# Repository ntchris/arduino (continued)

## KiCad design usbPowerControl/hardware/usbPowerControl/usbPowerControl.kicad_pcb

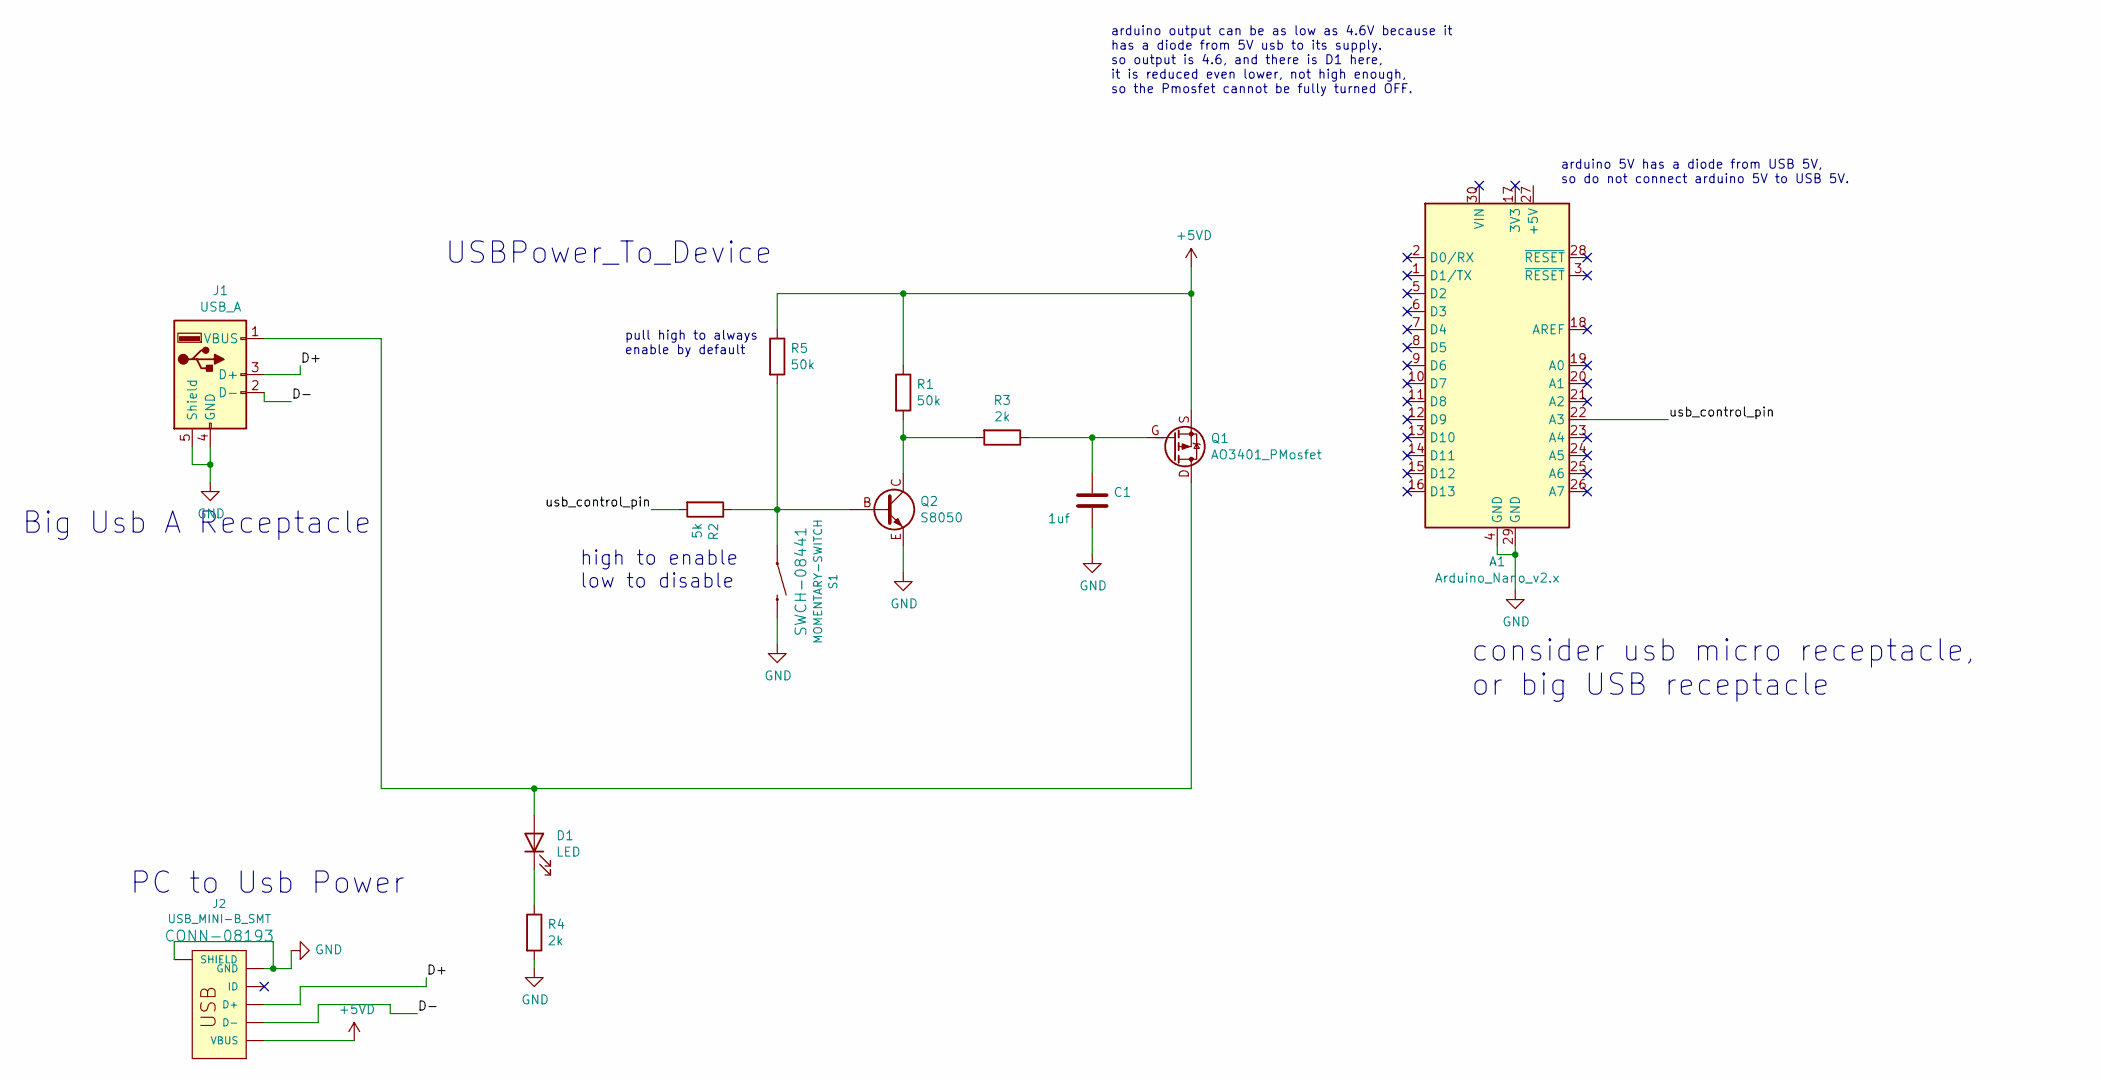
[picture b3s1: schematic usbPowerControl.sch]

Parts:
A1: Arduino_Nano_v2.x; Arduino_Nano
C1: 1uf; R_C_0805_2012Metric_Pad1.20x1.50mm_HandSolder
D1: LED; LED_D3.0mm
J1: USB_A; SAMTEC_USB-A-S-X-X-SM2
J2: USB_MINI-B_SMT; USB_Mini-B_Wuerth_65100516121_Horizontal
Q1: AO3401_PMosfet; SOT-23_PMOSFET
Q2: S8050; SOT-23_PNP_NPN
R1: 50k; R_C_0805_2012Metric_Pad1.20x1.50mm_HandSolder
R2: 5k; R_C_0805_2012Metric_Pad1.20x1.50mm_HandSolder
R3, R4: 2k; R_C_0805_2012Metric_Pad1.20x1.50mm_HandSolder
R5: 50k; R_1206_3216Metric_Pad1.30x1.75mm_HandSolder
S1: MOMENTARY-SWITCH; SW_Push_1P1T_NO_6x6mm_H9.5mm

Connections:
+5VD: J2.VBUS, Q1.S, R1.1, R5.1
/D+: J1.3 (D+), J2.D+
/D-: J1.2 (D-), J2.D-
/usb_control_pin: A1.22 (A3), R2.2
GND: A1.4 (GND), A1.29 (GND), C1.2, J1.4 (GND), J1.5 (Shield), J1.6, J2.GND, J2.S1 (SHIELD), J2.S2 (SHIELD), J2.S3 (SHIELD), J2.S4 (SHIELD), Q2.E, R4.2, S1.2
unnamed: C1.1, Q1.G, R3.1
unnamed: D1.A, J1.1 (VBUS), Q1.D
unnamed: D1.K, R4.1
unnamed: Q2.B, R2.1, R5.2, S1.1
unnamed: Q2.C, R1.2, R3.2

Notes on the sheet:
PC to Usb Power
USBPower_To_Device
Big Usb A Receptacle
consider usb micro receptacle, or big USB receptacle
arduino output can be as low as 4.6V because it has a diode from 5V usb to its supply. so output is 4.6, and there is D1 here, it is reduced even lower, not high enough, so the Pmosfet cannot be fully turned OFF.
high to enable low to disable
pull high to always enable by default
arduino 5V has a diode from USB 5V, so do not connect arduino 5V to USB 5V.

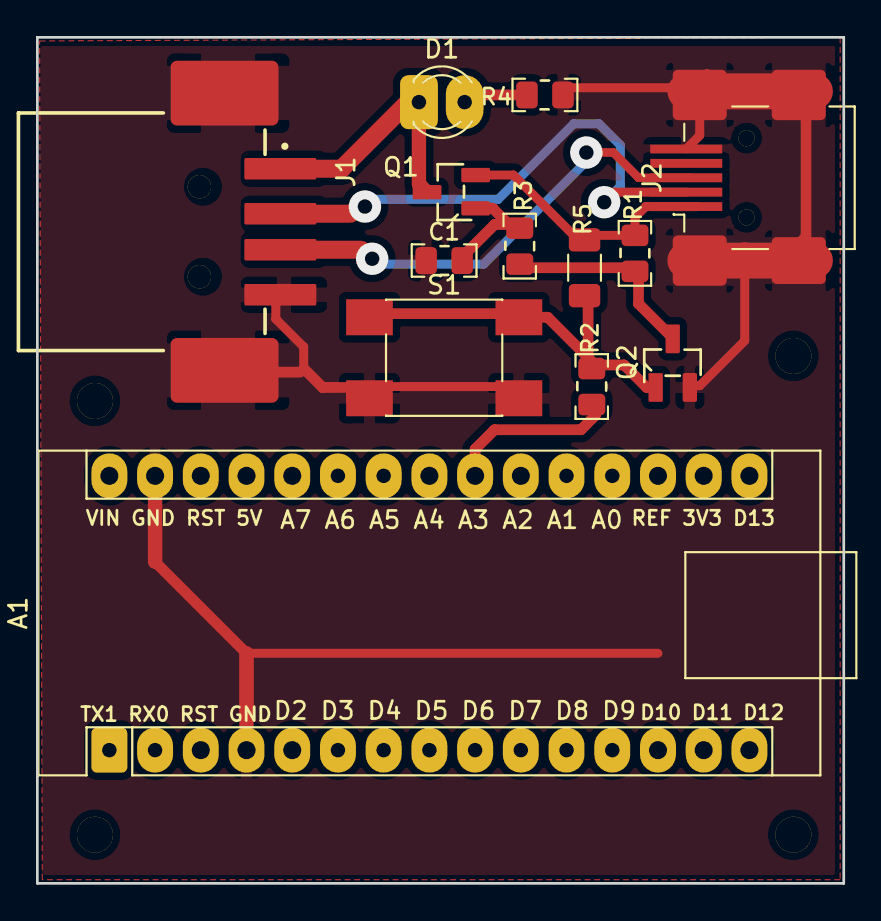
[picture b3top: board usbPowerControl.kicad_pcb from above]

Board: 2 copper layers, 44.8 x 47.0 mm, 13 parts (0 on the bottom side), 10 nets.

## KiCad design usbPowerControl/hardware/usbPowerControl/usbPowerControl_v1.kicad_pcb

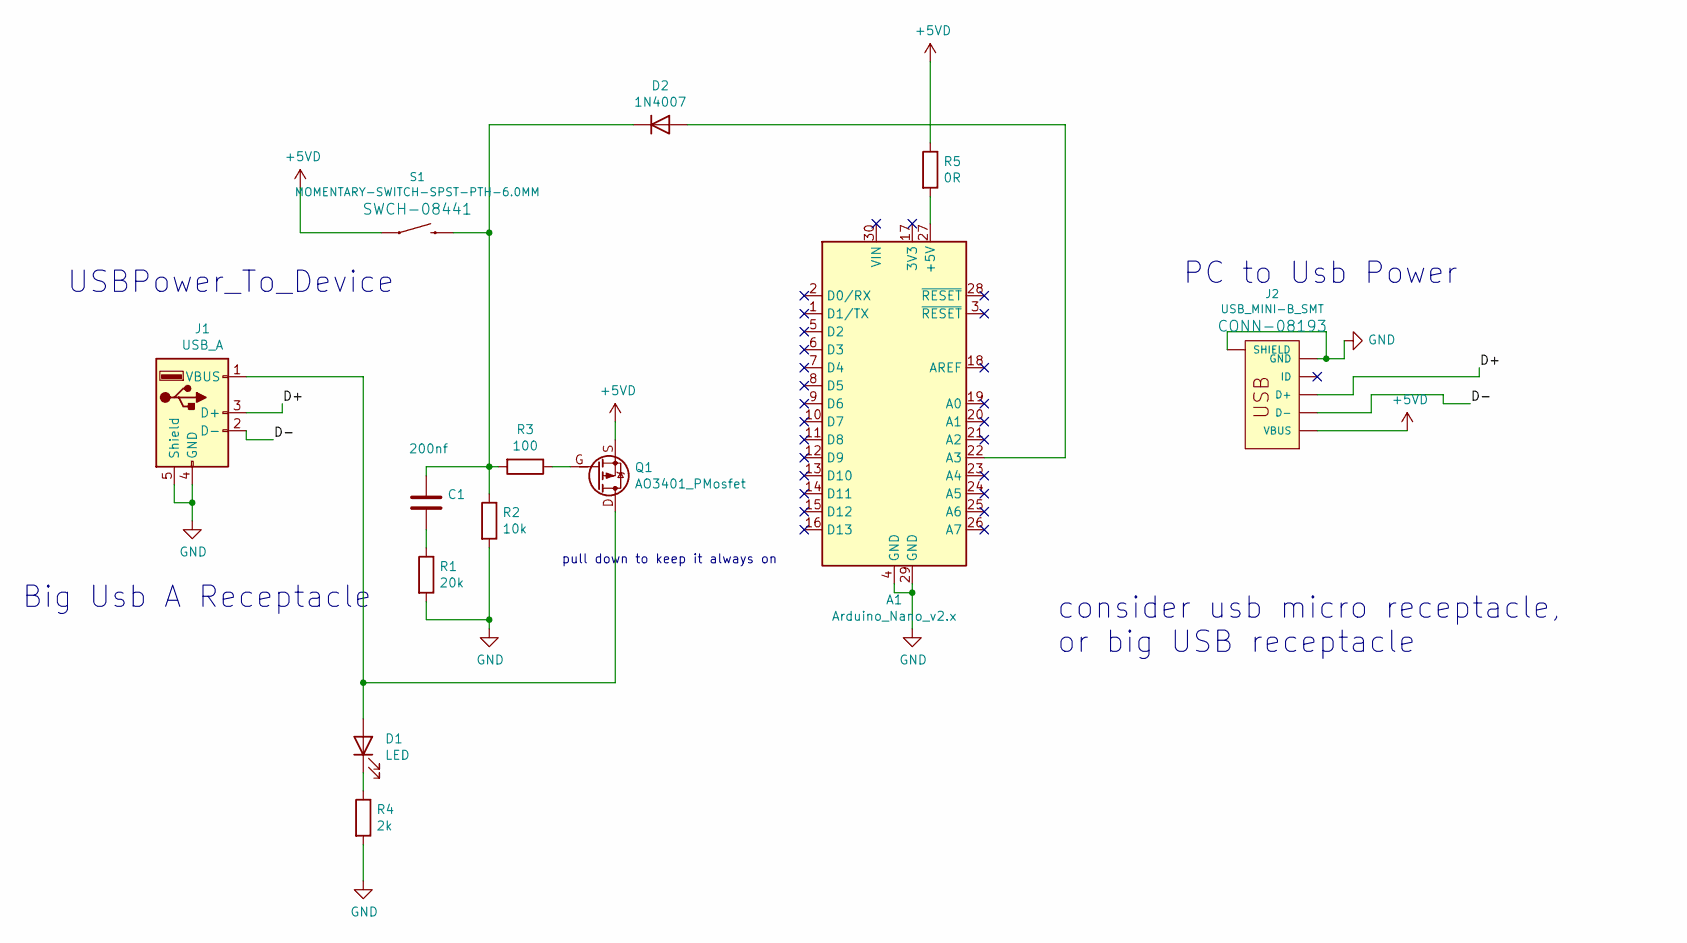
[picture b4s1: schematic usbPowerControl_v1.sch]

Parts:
A1: Arduino_Nano_v2.x; Arduino_Nano
C1: 200nf; R_C_0805_2012Metric_Pad1.20x1.50mm_HandSolder
D1: LED; LED_D3.0mm
D2: 1N4007; D_SOD-323_HandSoldering
J1: USB_A; SAMTEC_USB-A-S-X-X-SM2
J2: USB_MINI-B_SMT; USB_Mini-B_Wuerth_65100516121_Horizontal
Q1: AO3401_PMosfet; SOT-23_PMOSFET
R1: 20k; R_C_0805_2012Metric_Pad1.20x1.50mm_HandSolder
R2: 10k; R_C_0805_2012Metric_Pad1.20x1.50mm_HandSolder
R3: 100; R_C_0805_2012Metric_Pad1.20x1.50mm_HandSolder
R4: 2k; R_C_0805_2012Metric_Pad1.20x1.50mm_HandSolder
R5: 0R; R_C_0805_2012Metric_Pad1.20x1.50mm_HandSolder
S1: MOMENTARY-SWITCH-SPST-PTH-6.0MM; SW_Push_1P1T_NO_6x6mm_H9.5mm

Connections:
+5VD: J2.VBUS, Q1.S, R5.1, S1.1
/D+: J1.3 (D+), J2.D+
/D-: J1.2 (D-), J2.D-
GND: A1.4 (GND), A1.29 (GND), J1.4 (GND), J1.5 (Shield), J1.6, J2.GND, J2.S1 (SHIELD), J2.S2 (SHIELD), J2.S3 (SHIELD), J2.S4 (SHIELD), R1.2, R2.2, R4.2
unnamed: A1.22 (A3), D2.2 (A)
unnamed: A1.27 (+5V), R5.2
unnamed: C1.1, D2.1 (K), R2.1, R3.2, S1.2
unnamed: C1.2, R1.1
unnamed: D1.A, J1.1 (VBUS), Q1.D
unnamed: D1.K, R4.1
unnamed: Q1.G, R3.1

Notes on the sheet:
PC to Usb Power
USBPower_To_Device
Big Usb A Receptacle
consider usb micro receptacle, or big USB receptacle
pull down to keep it always on

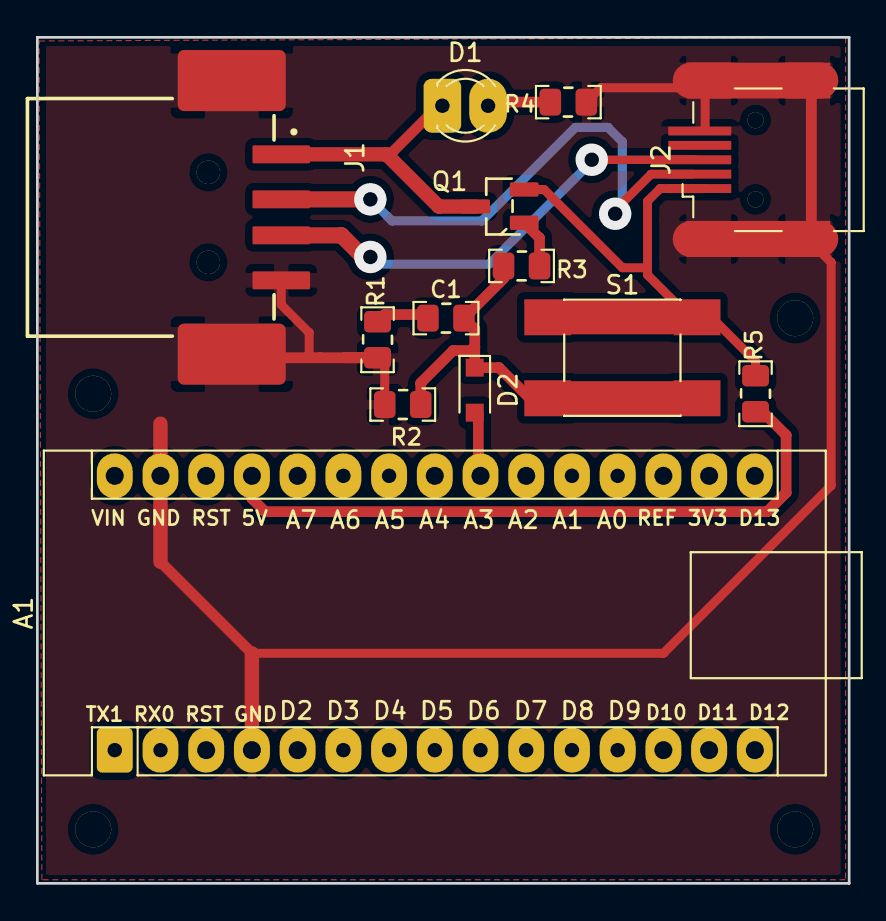
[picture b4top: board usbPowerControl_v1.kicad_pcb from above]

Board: 2 copper layers, 45.1 x 47.0 mm, 13 parts (0 on the bottom side), 11 nets.

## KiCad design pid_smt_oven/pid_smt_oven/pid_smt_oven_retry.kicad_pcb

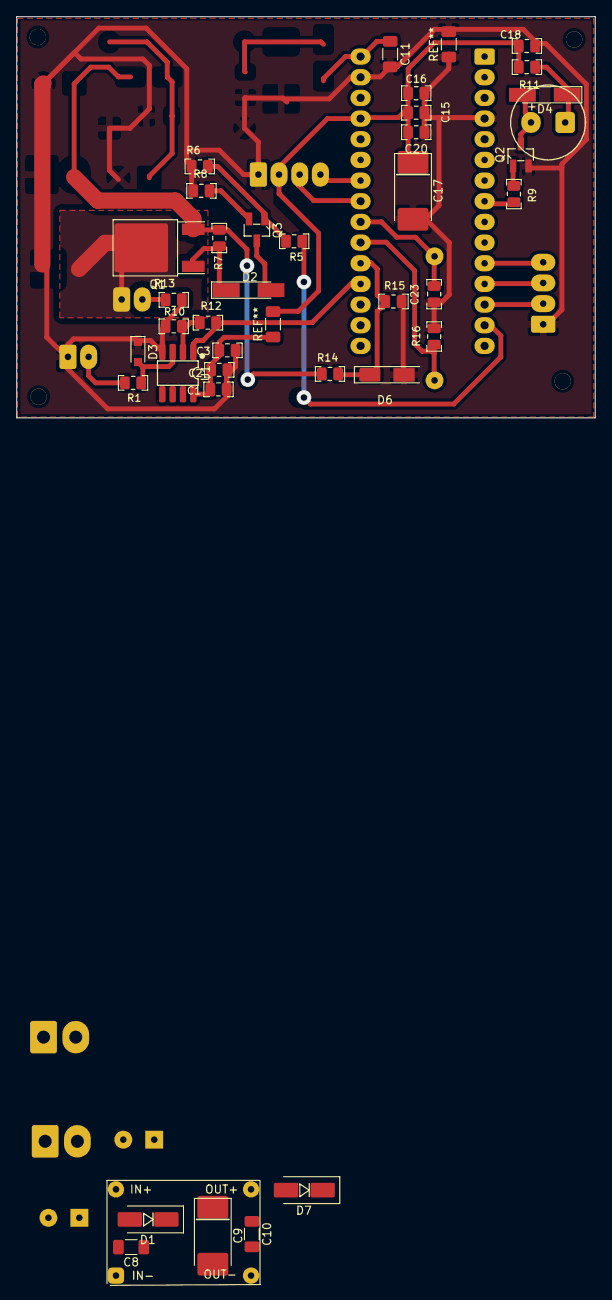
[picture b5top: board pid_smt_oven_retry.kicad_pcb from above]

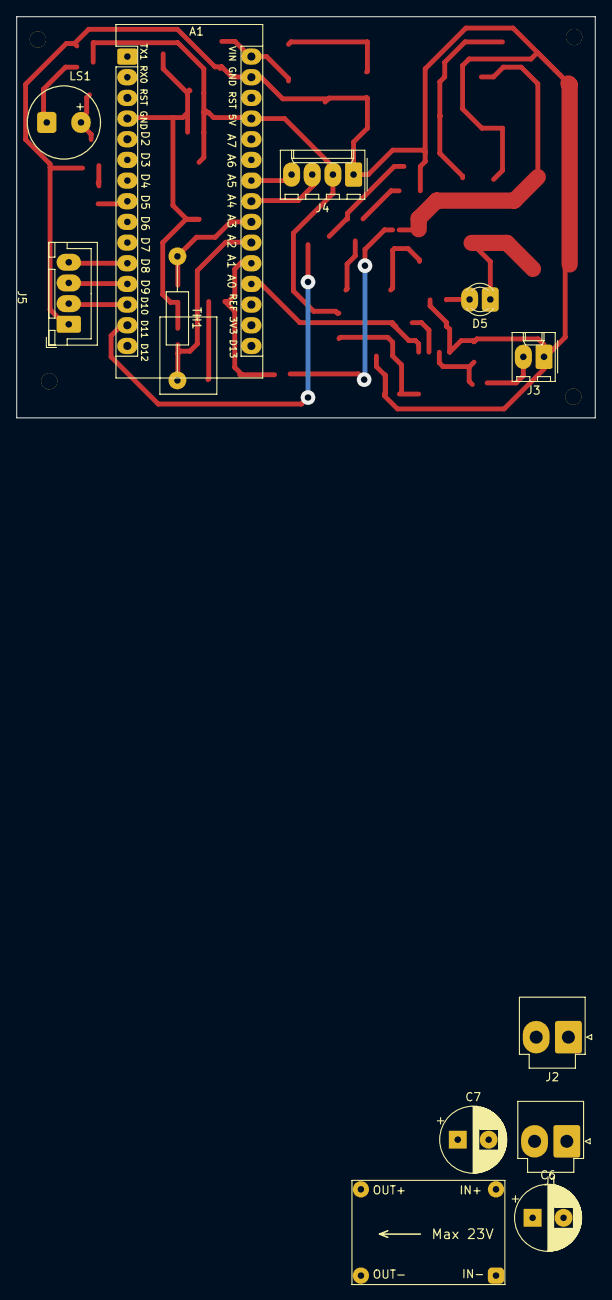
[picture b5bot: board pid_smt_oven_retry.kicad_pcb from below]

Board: 2 copper layers, 71.1 x 49.3 mm, 52 parts (12 on the bottom side), 29 nets.

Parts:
A1: Arduino_Nano_v2.x; Arduino_Nano
C1, C15, C18: 22uf; R_C_0805_2012Metric_Pad1.20x1.50mm_HandSolder
C2, C20, C23: 100nf; R_C_0805_2012Metric_Pad1.20x1.50mm_HandSolder
C3: 10nf; R_C_0805_2012Metric_Pad1.20x1.50mm_HandSolder
C6, C7: 470uf; CP_Radial_D8.0mm_P3.80mm
C8, C10: 22uf; C_1206_3216Metric_Pad1.33x1.80mm_HandSolder
C9, C17: 220uf; CP_EIA-7343-20_Kemet-V_Pad2.25x2.55mm_HandSolder
C11: 47uf; C_1206_3216Metric_Pad1.33x1.80mm_HandSolder
C16: 47uf; R_C_0805_2012Metric_Pad1.20x1.50mm_HandSolder
D1, D7: 1N4007; D_SMA_Handsoldering
D2: 5V; D_MiniMELF_Handsoldering
D3: 1N5819 S4; D_SOD-323_HandSoldering
D4: 1N4148; D_MiniMELF_Handsoldering
D5: LED; LED_D3.0mm
D6: 4v; D_MiniMELF_Handsoldering_Zener
H1, H2, H3, H4: MountingHole; MountingHole_2.0mm
J1: VH3.96_1X02 20V Power; JST_VH_B2P-VH-B_1x02_P3.96mm_Vertical
J2: Heater VH3.96_1X02; JST_VH_B2P-VH-B_1x02_P3.96mm_Vertical
J3: Thermo JST_2.54_1X02; Molex_KK-254_AE-6410-02A_1x02_P2.54mm_Vertical
J4: JST_2.54_1X04_LCD; Molex_KK-254_AE-6410-04A_1x04_P2.54mm_Vertical
J5: XH2.54_1X04_RotaryEnc; JST_XH_1x04_P2.54mm_Vertical
LS1: Speaker; Buzzer_9x4.2
Q1: AOD403_pmosfet; TO-252-2
Q2, Q3: S8050; SOT-23_PNP_NPN
R1: 10k; R_C_0805_2012Metric_Pad1.20x1.50mm_HandSolder
R5, R9, R13: 4k; R_C_0805_2012Metric_Pad1.20x1.50mm_HandSolder
R6: 18k; R_C_0805_2012Metric_Pad1.20x1.50mm_HandSolder
R7, R16: 2k; R_C_0805_2012Metric_Pad1.20x1.50mm_HandSolder
R8: 180; R_C_0805_2012Metric_Pad1.20x1.50mm_HandSolder
R10: 1k; R_C_0805_2012Metric_Pad1.20x1.50mm_HandSolder
R11: 280; R_C_0805_2012Metric_Pad1.20x1.50mm_HandSolder
R12: 240k; R_C_0805_2012Metric_Pad1.20x1.50mm_HandSolder
R14: 75k; R_C_0805_2012Metric_Pad1.20x1.50mm_HandSolder
R15: 20k; R_C_0805_2012Metric_Pad1.20x1.50mm_HandSolder
TH1: Thermistor_NTC 10k; R_Axial_DIN0207_L6.3mm_D2.5mm_P15.24mm_Horizontal
U1: MCP6002; SO-8_3.9x4.9mm_P1.27mm
a1: mini360_dcdc_stepdown; mini360_dcdc_buck_module

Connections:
20V: C6.1, D1.2, J1.2, Q1.S, R7.2, R14.1
/20VDetect: A1.20, D6.1, R14.2, R15.1
/V6.0: A1.30, C11.1, D7.1
/buzzerPwm: A1.8, R9.2
/enable_env_temp_check: A1.22, C23.1, TH1.1
/enable_heater: A1.14, R5.2
/env_temp_adc: A1.21, R16.1, TH1.2
/heaterPower: D5.A, J2.2, Q1.D
/opamp_to_adc: A1.19, R12.1, U1.1
/rot_button: A1.11, J5.4
/rot_left: A1.12, J5.3
/rot_right: A1.13, J5.2
/scl: A1.24, J4.4
/sda: A1.23, J4.3
/thermal_couple: J3.2, R1.2
GND: A1.4, A1.29, C1.2, C2.2, C3.2, C6.2, C7.2, C8.2, C9.2, C10.2, C11.2, C15.2, C16.2, C17.2, C18.2, C20.2, C23.2, D3.1, D6.2, J1.1, J2.1, J3.1, J4.1, J5.1, Q2.E, R6.2, R8.1, R10.2, R13.1, R15.2, R16.2, U1.4, a1.1, a1.4
unnamed: C7.1, C8.1, D1.1, a1.2
unnamed: C9.1, C10.1, D7.2, a1.3
unnamed: D2.1, Q1.G, R7.1
unnamed: D2.2, Q3.C
unnamed: D3.2, R1.1, U1.3
unnamed: D4.1, LS1.1, R11.2
unnamed: D4.2, LS1.2, Q2.C
unnamed: D5.K, R13.2
unnamed: Q2.B, R9.1
unnamed: Q3.B, R5.1, R6.1
unnamed: Q3.E, R8.2
unnamed: R10.1, R12.2, U1.2
V5.0: A1.27, C1.1, C2.1, C3.1, C15.1, C16.1, C17.1, C18.1, C20.1, J4.2, R11.1, U1.8

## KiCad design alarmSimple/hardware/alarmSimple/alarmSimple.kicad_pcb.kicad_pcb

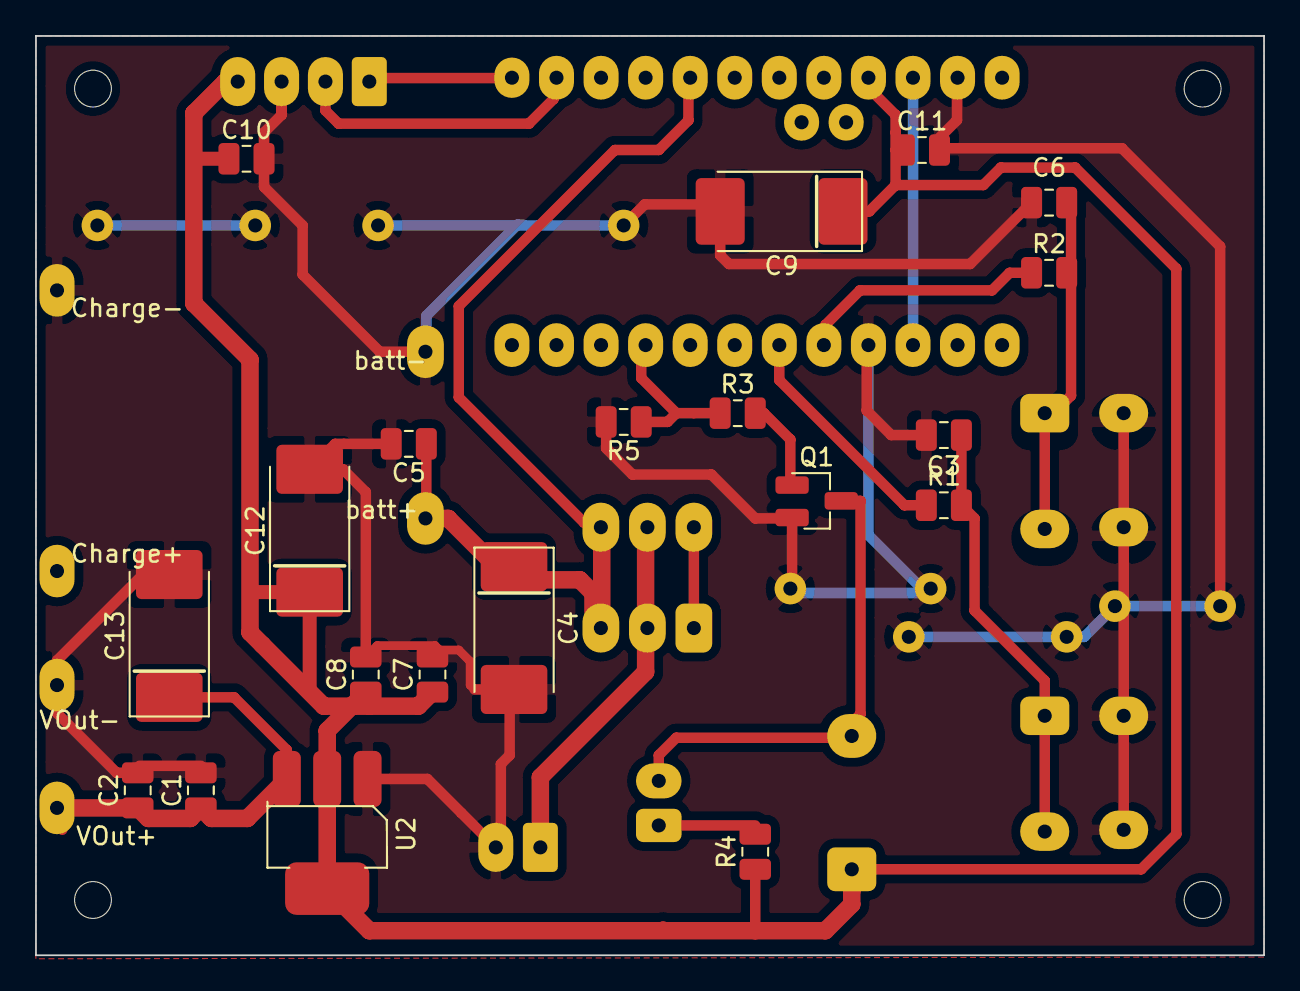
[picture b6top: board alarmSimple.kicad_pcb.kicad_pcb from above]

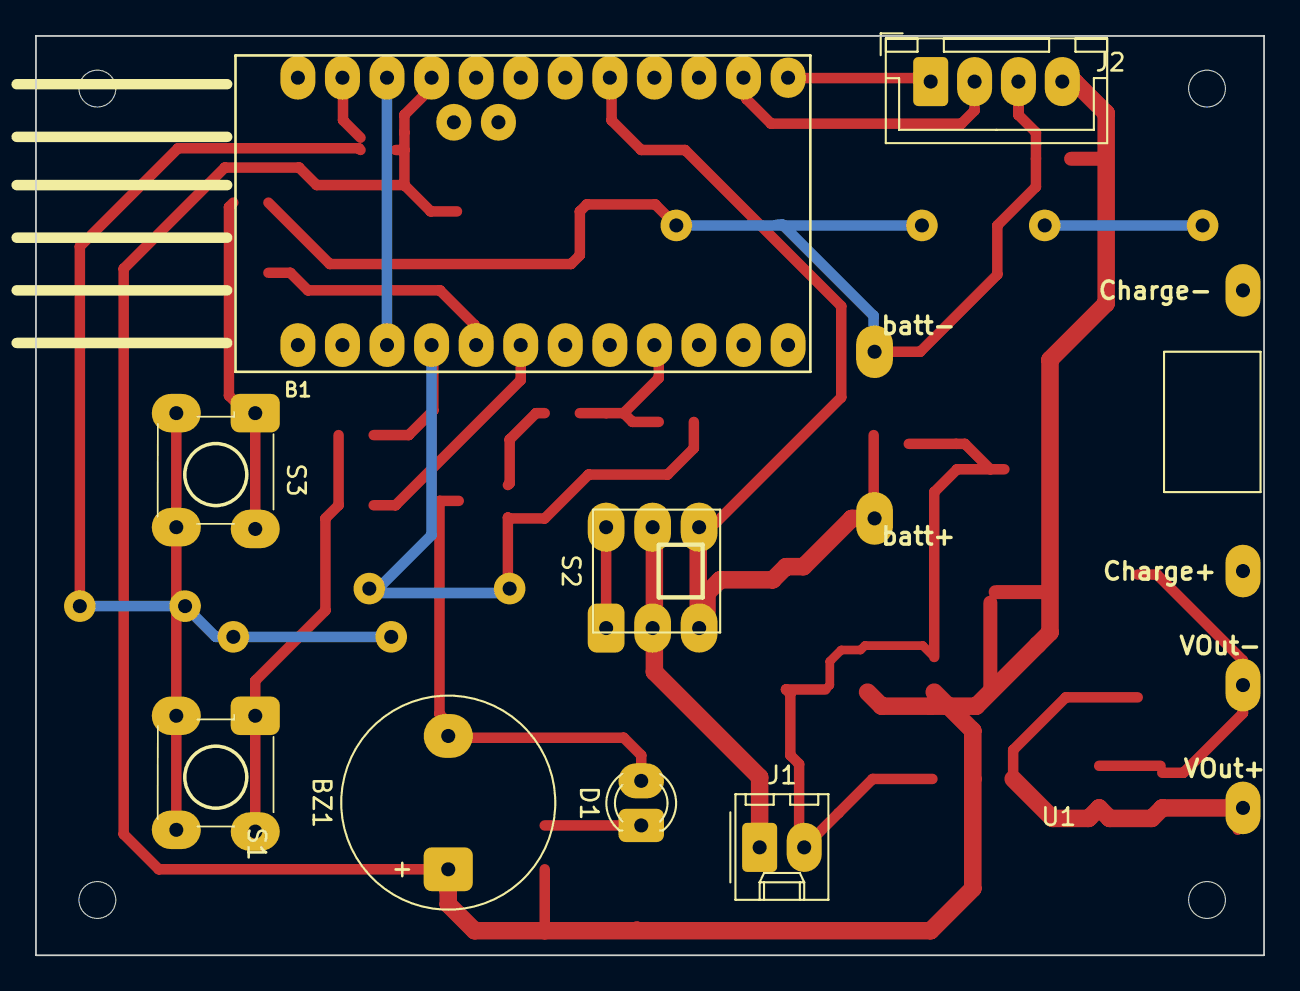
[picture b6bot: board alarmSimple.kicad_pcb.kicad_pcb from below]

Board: 2 copper layers, 70.0 x 52.4 mm, 30 parts (9 on the bottom side), 15 nets.

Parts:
 : MountingHole_2.1mm
B1: ARDUINO_PRO_MINI; arduino_pro_mini
BZ1: Buzzer; Buzzer_12x9.5RM7.6
C1: 20UF-0805-10V-10%; R_C_0805_2012Metric_Pad_HandSolder
C2, C5, C7, C8, C10, C11: 10UF-0805-10V-10%; R_C_0805_2012Metric_Pad_HandSolder
C3, C6: 100nf; R_C_0805_2012Metric_Pad_HandSolder
C4, C9, C12, C13: 220uf_227A; CP_EIA-7343-20_Kemet-V_Pad2.25x2.55mm_HandSolder
D1: LED3MM; LED_D3.0mm
J1: Batt; Molex_KK-254_AE-6410-02A_1x02_P2.54mm_Vertical
J2: Conn_01x04_Male; JST_XH_B4B-XH-A_1x04_P2.50mm_Vertical
Q1: AO3402_N_Mosfet; SOT-23_PMOSFET
R1, R2: 6.4k; R_C_0805_2012Metric_Pad_HandSolder
R3: 100R; R_C_0805_2012Metric_Pad_HandSolder
R4: 600R; R_C_0805_2012Metric_Pad_HandSolder
R5: 10kR; R_C_0805_2012Metric_Pad_HandSolder
S1, S3: MOMENTARY-SWITCH-SPST-PTH-6.0MM; Switch_Tactile_THT_6x6mm
S2: SWITCH-SPDT-PTH-11.6X4.0MM-KIT; SW_PUSH_LOCK__8.5mm_H8.5mm
U1: chargeBoostBoard; TC4056ChargeBoostBoard
U2: AMS1117-5.0; SOT-223-3_TabPin2

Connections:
+5V: B1.VCC, BZ1.1, C7.1, C8.1, C9.1, C10.1, C11.1, C12.1, J2.4, R4.1, U2.2
GND: B1.GND, C1.2, C2.2, C3.2, C4.2, C5.2, C6.2, C7.2, C8.2, C9.2, C10.2, C11.2, C12.2, C13.2, J1.2, J2.3, Q1.S, R5.2, S1.2, S3.2, U1.1, U1.3, U1.6, U2.1
unnamed: B1.10, J2.1
unnamed: B1.11, J2.2
unnamed: BZ1.2, D1.K, Q1.D
unnamed: C1.1, C2.1, C13.1, U1.4, U2.3
unnamed: C3.1, R1.2, S1.1
unnamed: C6.1, R2.2, S3.1
unnamed: D1.A, R4.2
unnamed: J1.1, S2.signal
unnamed: Q1.G, R3.2
VBattCheck: B1.A0, C4.1, C5.1, S2.close, U1.5
button_minus: B1.2, R2.1
button_plus: B1.3, R1.1
buzz_en: B1.6, R3.1, R5.1

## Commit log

2016-01-09 :octocat: Added .gitattributes
2016-01-09 Arduino first submission
    Arduino first submission
2016-05-01 First MCU AT89S51 digit tube display and counter
    First MCU AT89S51 digit tube display and counter
2016-05-02 using interrupt
2016-05-03 final , counter ready
2016-06-03 submit hex file
2016-11-29 start my TM1637 arduino project
    start my TM1637 arduino project
2016-11-29 first commit for TM1637 project
2016-11-29 delete , not in the right folder
    delete , not in the right folder
2016-12-02 Add files via upload
    it can show positive integer
2016-12-03 refactor
    add a myI2CDriver class so hopefully other ICs could reuse it.
2016-12-03 all ready
    support dot and string.
2016-12-04 supports overflow
    supports overflow
2016-12-04 error handling and set brightness
    error handling and set brightness
2016-12-04 final
2016-12-26 Create LICENSE
2018-01-22 submit a lot changes in a year
2018-01-22 minor change
2018-01-24 submit timer delay shut down project
2018-01-25 relay delay prototype is finished.
2018-01-26 reset key value if fail to get ack
2018-02-12 submit rotary encoder driver code
2018-02-13 make the rotary encoder a class
2018-02-15 change class name to super, DIO mode using input
2018-02-15 timerDigit tube project change lib name using super
    also remove hex files
2018-02-18 soldar station temp controller
    soldar station temp controller
2018-02-19 1st working draft of solder controller
2018-02-20 display less
2018-03-03 pcb design done
2018-03-03 update lib i2c dio using input pullup
2018-03-04 redraw pcb
2018-03-11 diy solder in progress also update tm1637 to display more letters
2018-03-11 rotary encoder improvement
2018-03-13 update tm1637 lib to support more chars
2018-03-13 submit draft program and schematic
2018-03-13 adding new change for disable enable heaters
2018-03-13 fix can't compile in linux problem
2018-03-13 now can compile in linux
2018-03-14 working in progress
2018-03-15 WIP, balance
2018-03-15 change heater name, don't check red and brown everytime
2018-03-15 all working well
2018-03-16 power on , heater off as default
2018-03-19 format only
2019-01-07 more change to solder station
2019-01-09 fix some warning for i2c driver and tm1637 driver
2019-01-09 developing
2019-01-10 working in progress PID
    do not disable and delay when it's already disabled
2019-01-11 working
2019-01-12 working well
    finished, until next time, add new features
2020-01-24 garage door alarm 433mhz done
    garage door alarm 433mhz done
2020-06-11 adding capacitor and using interrupt
    using capacitor, no need debounce.
2020-06-12 support button
2020-06-12 minor comment added
2020-06-13 add set min max function
2020-06-17 work in progress
    pid, pwm, modify pcb
2020-06-17 basically working
2020-06-17 submit the excel lookup table
2020-06-26 Create servo_door_trap.ino
    open source chipmunk trap
2020-07-07 submit working version for solder station new version
    submit working version for solder station new version
2020-07-08 90% finished
    90% finished
2020-07-10 V4 and V5
    V5 isfor order
    change some pins
2020-07-10 pcb drawing done for order
2020-07-11 order
2020-07-11 remove old files
2020-07-11 remove
2020-07-14 clean up and reorg
2021-02-04 solder station keep improving
    solder station keep improving
2021-06-09 rename tm1637 filename and add more char support
    rename tm1637 filename and add more char support
2021-06-09 simple alarm work in progress
    simple alarm work in progress
2021-06-14 finish arduino simple alarm design
    finish arduino simple alarm design
2021-06-14 add pcb step file
2021-06-16 enable low power saving mode
    enable low power saving mode for MCU
    disable servo so no more random tiny movement which drains the battery so quickly
2021-08-02 enhanced power saving mod
    enhanced power saving mod
    sleeping, interrupt wake up.
2021-08-13 support save target temp
    support save target temp
2021-08-15 fix a eeprom write bug which couldn't handle integer >255
    fix a eeprom write bug which couldn't handle integer >255
2021-08-31 clean up some old project DIY weller solder station
2021-10-11 adding usb power controller
2021-10-16 add some documentation
2021-10-17 KType thermocouple API
    KType thermocouple API
2021-11-05 enhance super rotary encoder lib
    to support fast rotate function,
    increase step in such case.
2021-11-08 PID surface mount oven controller
    oven or heating plate for smt.
    arduino
2021-11-18 working well
2022-12-06 major update software
    now use LCD2004
    change another PID algo
2023-01-02 added 120VAC and fixed a NTC bug
    added 120VAC and fixed a NTC bug
